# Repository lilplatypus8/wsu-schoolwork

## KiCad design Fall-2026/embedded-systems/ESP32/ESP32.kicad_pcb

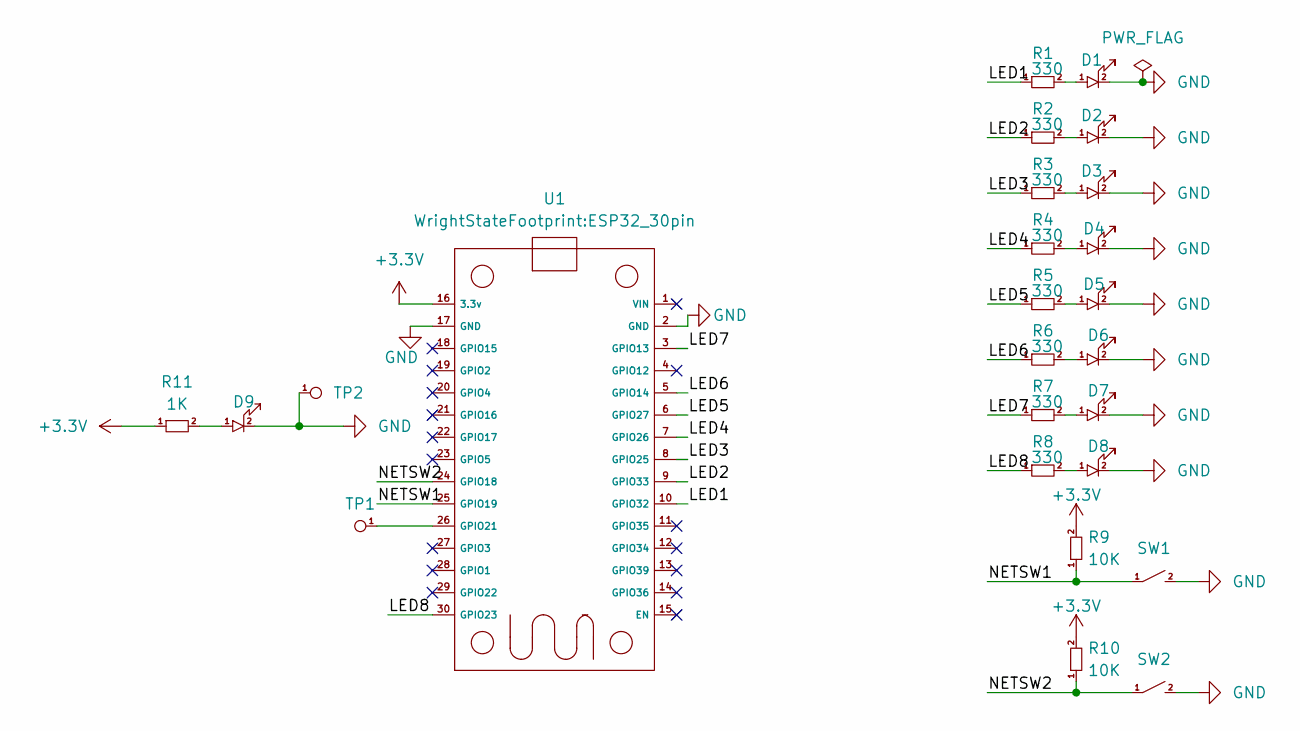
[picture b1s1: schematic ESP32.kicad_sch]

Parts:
D1, D2, D3: Red; LED_0603_1608Metric_Pad1.05x0.95mm_HandSolder; ManufacturerPartNumber LTST-C190KRKT
D4, D5: Yellow; LED_0603_1608Metric_Pad1.05x0.95mm_HandSolder; ManufacturerPartNumber LTST-C190KSKT
D6, D7, D8, D9: Green; LED_0603_1608Metric_Pad1.05x0.95mm_HandSolder; ManufacturerPartNumber LTST-C190GKT
R1, R2, R3, R4, R5, R6, R7, R8: 330; R_0603_1608Metric; ManufacturerPartNumber RC0603FR-07330RL
R9, R10: 10K; R_0603_1608Metric; ManufacturerPartNumber RC0603FR-0710KL
R11: 1K; R_0603_1608Metric; ManufacturerPartNumber RC0603FR-071KL
SW1, SW2: TL2233; ManufacturerPartNumber B3U-1000P
TP1, TP2: TestPoint_Pad_D2.0mm; ManufacturerPartNumber 36-5001-ND
U1: ESP32_30pin

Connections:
+3.3V: R9.2, R10.2, R11.1, U1.16 (3.3v)
/LED1: R1.1, U1.10 (GPIO32)
/LED2: R2.1, U1.9 (GPIO33)
/LED3: R3.1, U1.8 (GPIO25)
/LED4: R4.1, U1.7 (GPIO26)
/LED5: R5.1, U1.6 (GPIO27)
/LED6: R6.1, U1.5 (GPIO14)
/LED7: R7.1, U1.3 (GPIO13)
/LED8: R8.1, U1.30 (GPIO23)
/NETSW1: R9.1, SW1.1, U1.25 (GPIO19)
/NETSW2: R10.1, SW2.1, U1.24 (GPIO18)
GND: D1.2, D2.2, D3.2, D4.2, D5.2, D6.2, D7.2, D8.2, D9.2, SW1.2, SW2.2, TP2.1, U1.2 (GND), U1.17 (GND); also elsewhere on the board
unnamed: D1.1, R1.2
unnamed: D2.1, R2.2
unnamed: D3.1, R3.2
unnamed: D4.1, R4.2
unnamed: D5.1, R5.2
unnamed: D6.1, R6.2
unnamed: D7.1, R7.2
unnamed: D8.1, R8.2
unnamed: D9.1, R11.2
unnamed 21: TP1.1, U1.26 (GPIO21); also elsewhere on the board

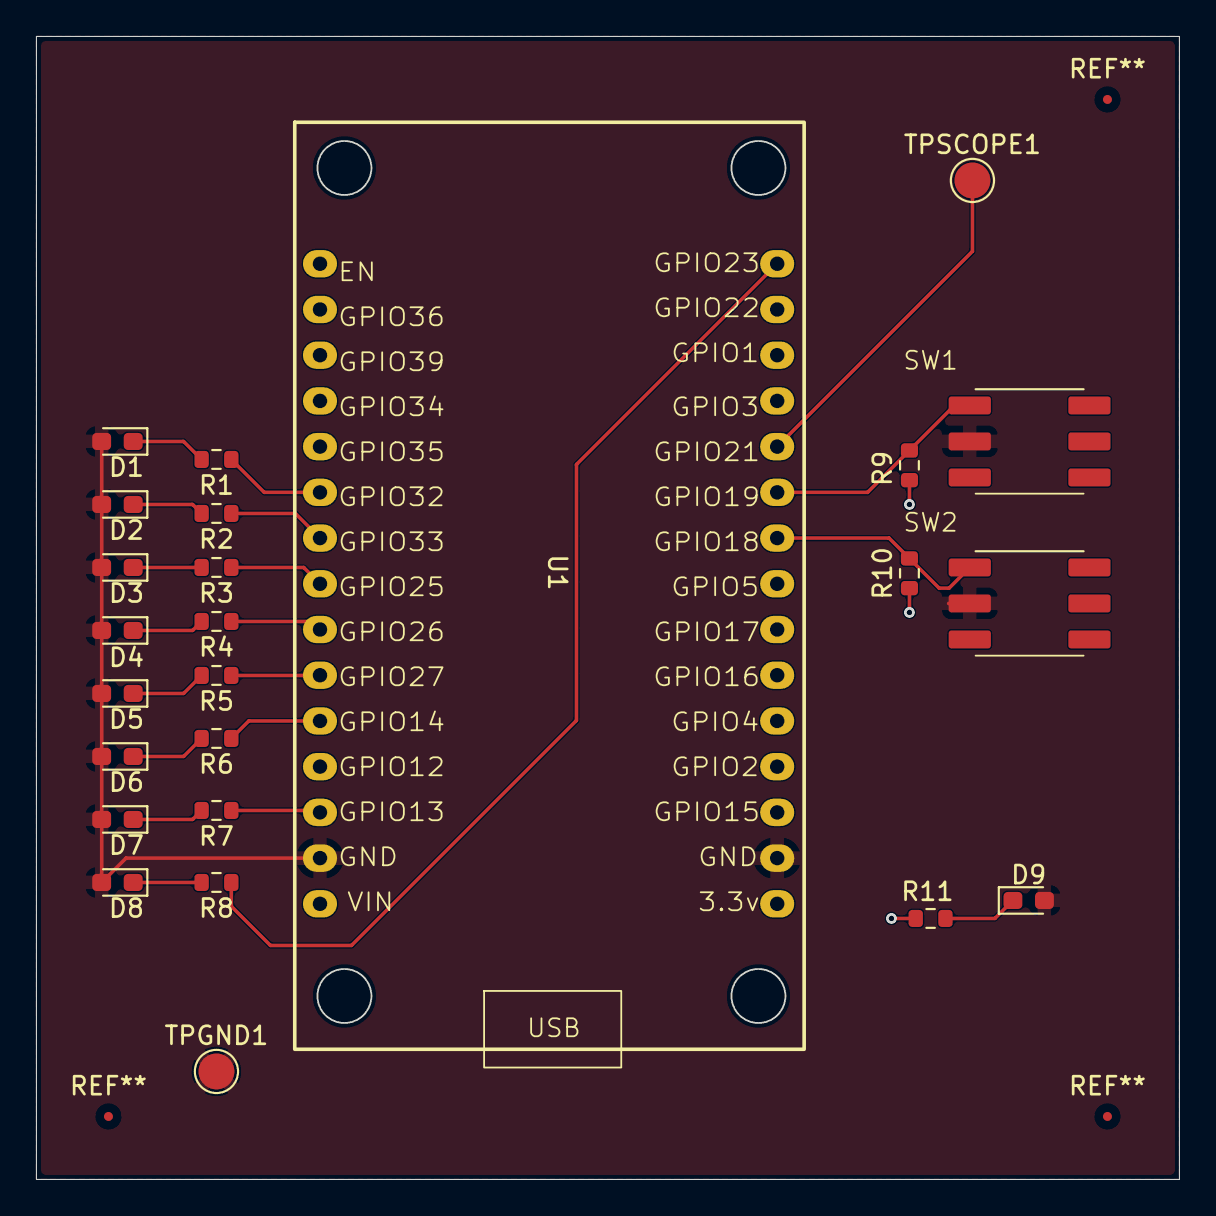
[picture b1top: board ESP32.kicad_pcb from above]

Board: 2 copper layers, 63.4 x 63.5 mm, 25 parts (0 on the bottom side), 22 nets.

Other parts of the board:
TPGND1: TestPoint_Pad_D2.0mm
TPSCOPE1: TestPoint_Pad_D2.0mm

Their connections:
GND: TPGND1.1; also elsewhere on the board
unnamed 21: TPSCOPE1.1; also elsewhere on the board

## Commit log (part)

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2025-05-01 Inital Files Added
2025-06-16 added os internals slides
2025-07-28 Add all slides
2025-07-28 removed excess slides and added final exam slide
2025-07-30 added gpt-generated notes for final
2025-08-27 add fall 2025 folder
2025-08-28 Added host-computer-security class and removed a notesheet
2025-09-02 exercise set 1 logic for cs done
2025-09-03 working on logic set 2
2025-09-03 lab 2 host computer security
2025-09-04 finished logic set 2
2025-09-05 working on white paper
2025-09-05 finished white paper
2025-09-08 working on logic set 3
2025-09-08 almost done set 3
2025-09-09 finished exercise set 3 for logic
2025-09-10 host security module 3 assignment
2025-09-10 finished comp languages project 1
2025-09-11 added folder for team projects
2025-09-15 comparative languages added
2025-09-20 working on comp languages project 2
2025-09-20 finished mergesort comp languages project 2
2025-09-22 finished powerset comp languages project 2
2025-09-26 finished comp languages project 2
2025-09-26 module 5 assignment host computer security done
2025-09-29 started exercise set 4 logic
2025-09-30 working on logic exercise set 4
2025-10-01 finished exercise set 4 logic
2025-10-03 working on exam 1 for comp languages
2025-10-05 tentatively finished comp languages exam 1
2025-10-08 working on logic exercise 5
2025-10-08 try again
2025-10-11 working on comp languages project 3
2025-10-13 finished comp languages project 3
2025-10-13 working on logic exercise 6
2025-10-14 finished logic exercise 6
2025-10-22 almost done comp languages project 4
2025-10-23 finished project 4 comp languages
2025-10-28 working on logic exercise 7
2025-10-29 still working exercise 7 logic
2025-10-30 finished exercise 7 logic
2025-11-04 working on logic exercise 8
2025-11-05 finished logic exercise 8
2025-11-06 working on project 5 comp languages
2025-11-07 almost done project 5 comp languages
2025-11-07 finished project 5 comp languages
2025-11-07 working on module 11 assignment
2025-11-13 working on logic exercise 9
2025-11-17 finished exercise 9 logic
2025-11-19 working on comp languages project 6 and host security assignment 13
2025-11-19 finished project 6 comp languages
2025-11-23 finished host security module 13 assignment
2025-11-27 small tweaks to comp languages project 6
2025-11-27 working on comp languages project 7
2025-12-01 finished comp languages project 7
2025-12-08 finished comp languages final
2026-02-09 added quantum gates work
2026-02-11 working on quantum gates homework
2026-02-13 created cyber network security folder
2026-02-19 set up venv for windows
2026-02-27 finished quantum homework
2026-04-02 finished quantum homework 2
2026-04-14 finished cyber network project 3
2026-04-22 finished cyber network security project 4
